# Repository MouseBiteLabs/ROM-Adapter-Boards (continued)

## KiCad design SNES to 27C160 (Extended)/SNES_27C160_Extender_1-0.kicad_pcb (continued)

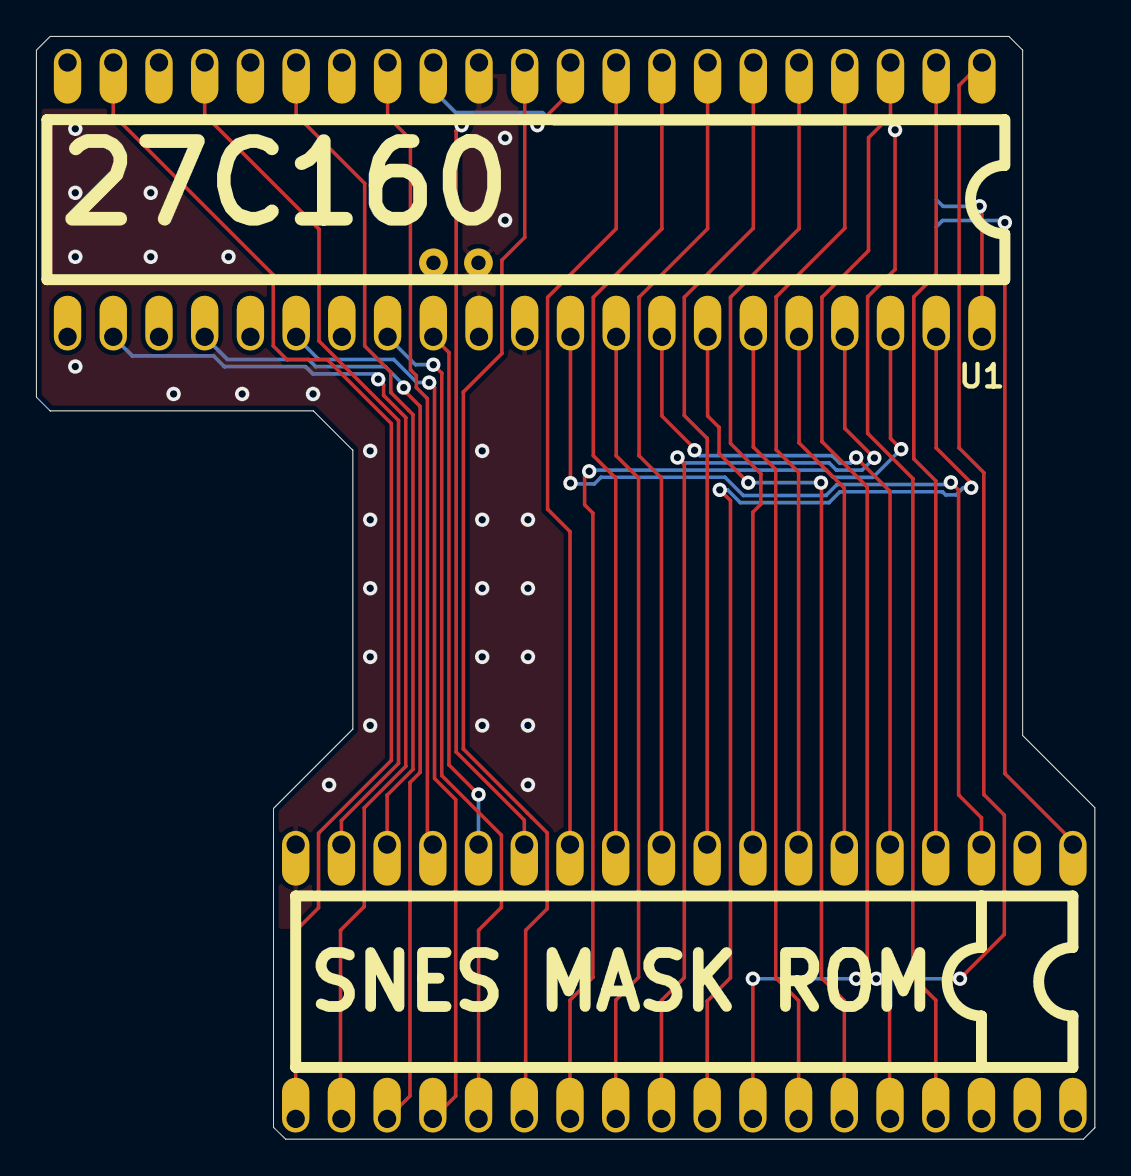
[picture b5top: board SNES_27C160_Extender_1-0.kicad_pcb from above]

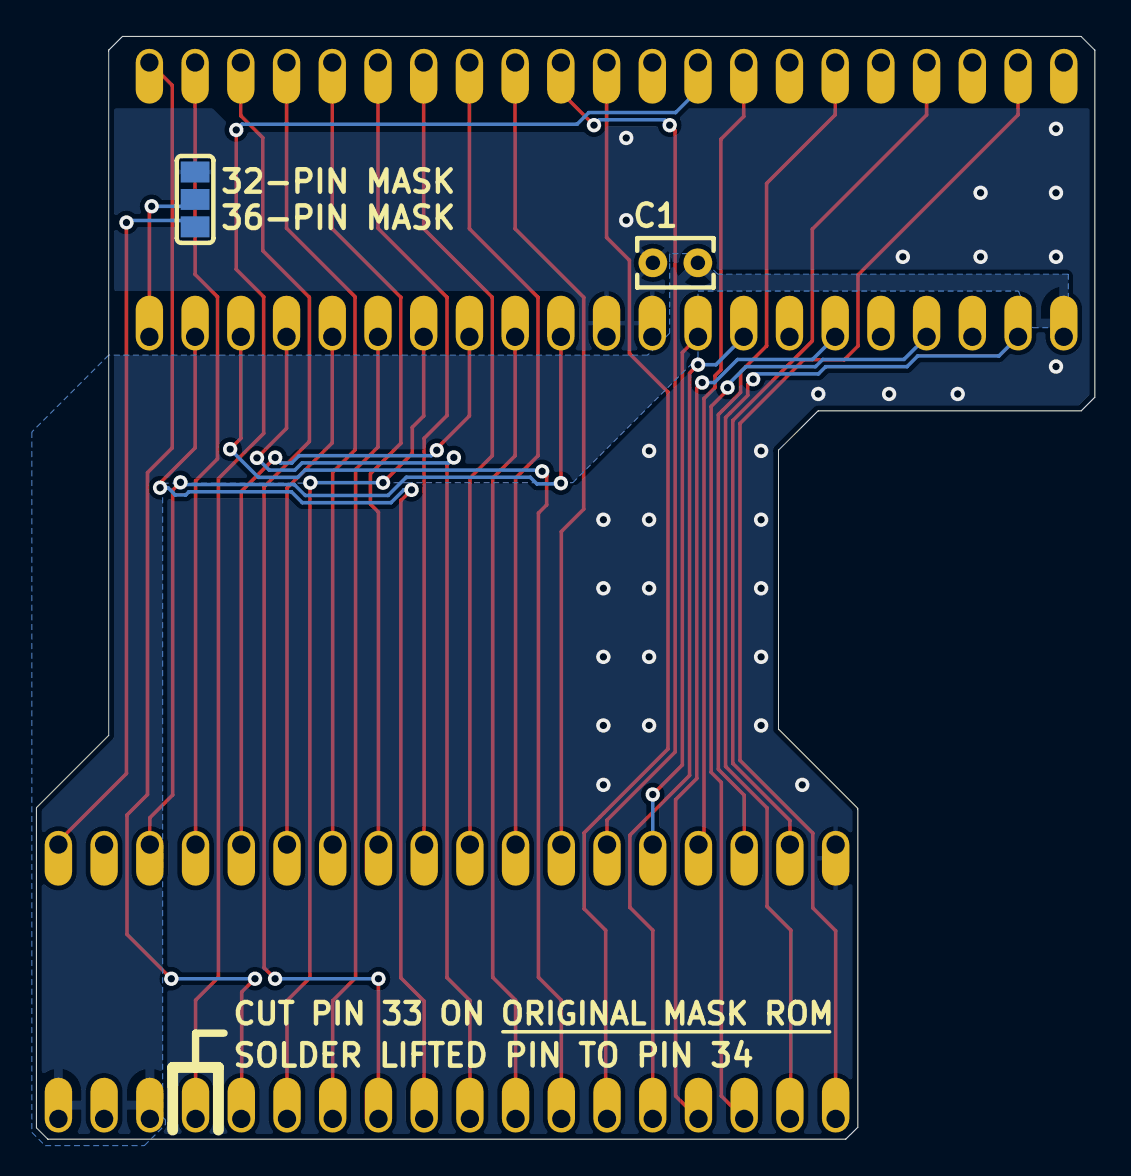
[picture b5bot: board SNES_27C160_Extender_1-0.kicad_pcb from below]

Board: 2 copper layers, 58.8 x 61.3 mm, 4 parts (2 on the bottom side), 34 nets.

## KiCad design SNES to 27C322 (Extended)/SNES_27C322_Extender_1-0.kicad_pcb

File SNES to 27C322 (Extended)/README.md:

# SNES Mask ROM to 27C322 (Extended)

**Design is intended for personal use only, not for modifying existing cartridges for commercial sale.** I really would rather you *not* use these adapter boards to repurpose old carts into rarer games or ROM hacks in order to sell them commercially. Use a brand new cart circuit board instead! I have plenty to choose from :)

Instructions: https://mousebitelabs.com/2020/01/28/27c322-27c160-to-snes-mask-rom-extended-adapter-board/

OSH Park: https://oshpark.com/shared_projects/NkhvILAe (sorry it's expensive but tariffs ain't making these any cheaper from overseas)

## License

<br />This work is licensed under a <a rel="license" href="http://creativecommons.org/licenses/by-sa/4.0/">Creative Commons Attribution-ShareAlike 4.0 International License</a>. You are able to copy and redistribute the material in any medium or format, as well as remix, transform, or build upon the material for any purpose (even commercial) - but you **must** give appropriate credit, provide a link to the license, and indicate if any changes were made.

©MouseBiteLabs 2025

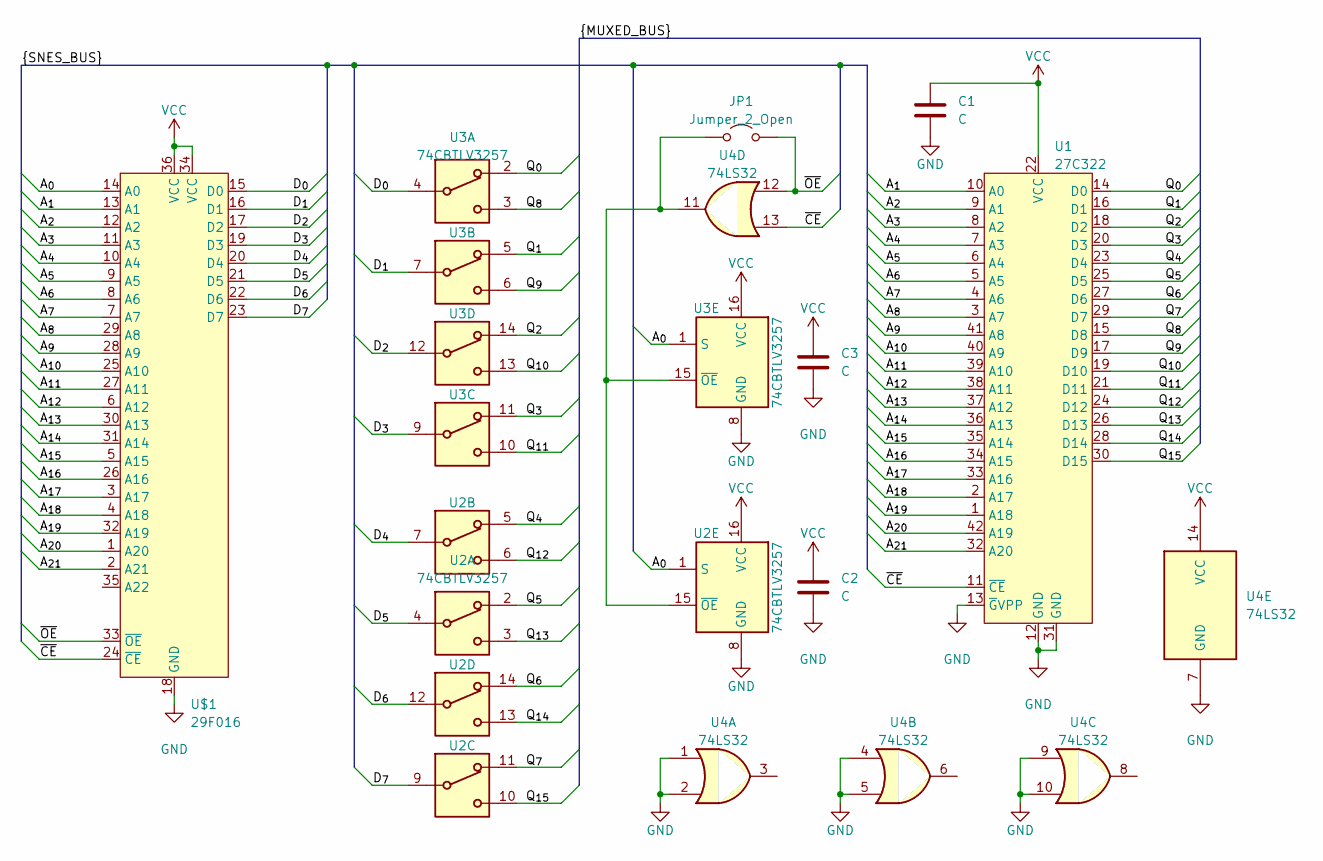
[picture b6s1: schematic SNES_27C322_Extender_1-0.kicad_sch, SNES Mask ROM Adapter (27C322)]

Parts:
C1, C2, C3: C; C_THT
JP1: Jumper_2_Open; SJ
U1: 27C322; PDIP_42_Offset_Pads
U2, U3: 74CBTLV3257; DIP-16_W7.62mm
U4: 74LS32; DIP-14_W7.62mm
U$1: 29F016; 36-PDIP

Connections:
/A_{0}: U2.1 (S), U3.1 (S), U$1.14 (A0)
/A_{1}: U1.10 (A0), U$1.13 (A1)
/A_{2}: U1.9 (A1), U$1.12 (A2)
/A_{3}: U1.8 (A2), U$1.11 (A3)
/A_{4}: U1.7 (A3), U$1.10 (A4)
/A_{5}: U1.6 (A4), U$1.9 (A5)
/A_{6}: U1.5 (A5), U$1.8 (A6)
/A_{7}: U1.4 (A6), U$1.7 (A7)
/A_{8}: U1.3 (A7), U$1.29 (A8)
/A_{9}: U1.41 (A8), U$1.28 (A9)
/A_{10}: U1.40 (A9), U$1.25 (A10)
/A_{11}: U1.39 (A10), U$1.27 (A11)
/A_{12}: U1.38 (A11), U$1.6 (A12)
/A_{13}: U1.37 (A12), U$1.30 (A13)
/A_{14}: U1.36 (A13), U$1.31 (A14)
/A_{15}: U1.35 (A14), U$1.5 (A15)
/A_{16}: U1.34 (A15), U$1.26 (A16)
/A_{17}: U1.33 (A16), U$1.3 (A17)
/A_{18}: U1.2 (A17), U$1.4 (A18)
/A_{19}: U1.1 (A18), U$1.32 (A19)
/A_{20}: U1.42 (A19), U$1.1 (A20)
/A_{21}: U1.32 (A20), U$1.2 (A21)
/D_{0}: U3.4, U$1.15 (D0)
/D_{1}: U3.7, U$1.16 (D1)
/D_{2}: U3.12, U$1.17 (D2)
/D_{3}: U3.9, U$1.19 (D3)
/D_{4}: U2.7, U$1.20 (D4)
/D_{5}: U2.4, U$1.21 (D5)
/D_{6}: U2.12, U$1.22 (D6)
/D_{7}: U2.9, U$1.23 (D7)
/Q_{0}: U1.14 (D0), U3.2
/Q_{1}: U1.16 (D1), U3.5
/Q_{2}: U1.18 (D2), U3.14
/Q_{3}: U1.20 (D3), U3.11
/Q_{4}: U1.23 (D4), U2.5
/Q_{5}: U1.25 (D5), U2.2
/Q_{6}: U1.27 (D6), U2.14
/Q_{7}: U1.29 (D7), U2.11
/Q_{8}: U1.15 (D8), U3.3
/Q_{9}: U1.17 (D9), U3.6
/Q_{10}: U1.19 (D10), U3.13
/Q_{11}: U1.21 (D11), U3.10
/Q_{12}: U1.24 (D12), U2.6
/Q_{13}: U1.26 (D13), U2.3
/Q_{14}: U1.28 (D14), U2.13
/Q_{15}: U1.30 (D15), U2.10
/~CE: U1.11 (~CE), U4.13, U$1.24 (~CE)
/~OE: JP1.2 (B), U4.12, U$1.33 (~OE)
GND: C1.2, C2.2, C3.2, U1.12 (GND), U1.13 (~GVPP), U1.31 (GND), U2.8 (GND), U3.8 (GND), U4.1, U4.2, U4.4, U4.5, U4.7 (GND), U4.9, U4.10, U$1.18 (GND)
unnamed: JP1.1 (A), U2.15 (~OE), U3.15 (~OE), U4.11
VCC: C1.1, C2.1, C3.1, U1.22 (VCC), U2.16 (VCC), U3.16 (VCC), U4.14 (VCC), U$1.34 (VCC), U$1.36 (VCC)

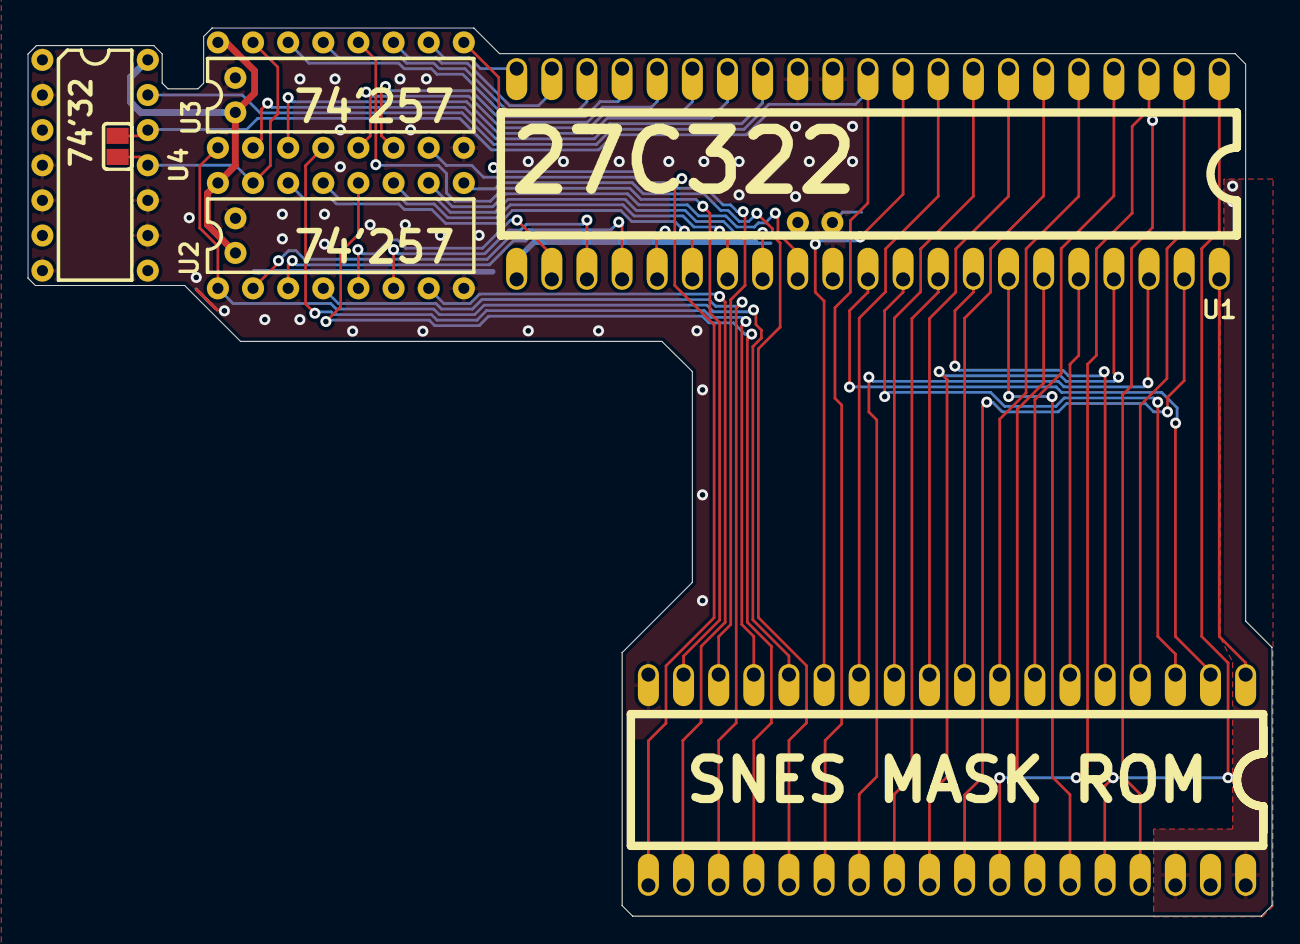
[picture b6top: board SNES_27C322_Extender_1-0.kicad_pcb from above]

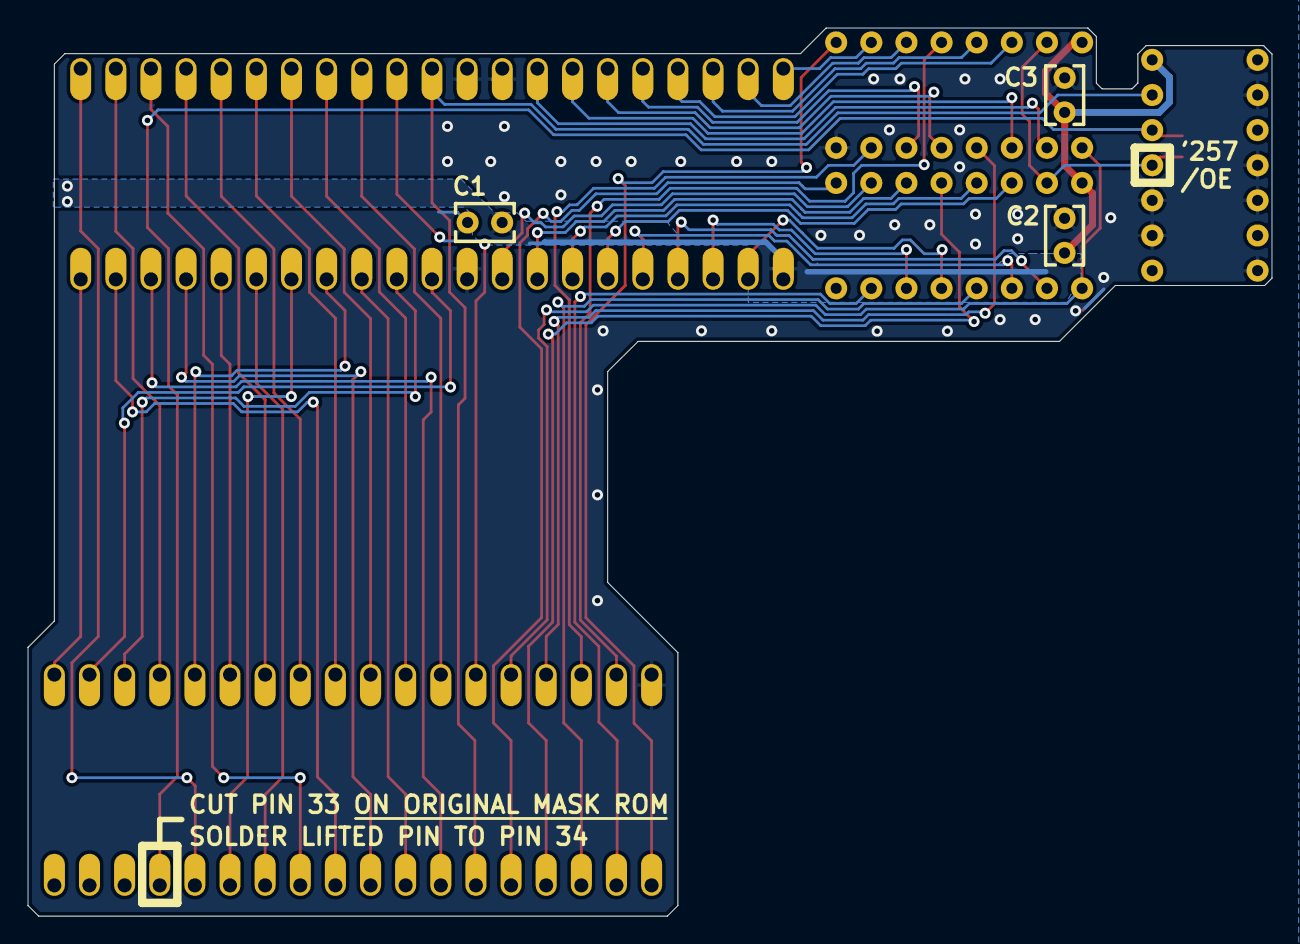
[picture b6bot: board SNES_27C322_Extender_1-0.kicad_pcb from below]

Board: 2 copper layers, 89.9 x 64.2 mm, 9 parts (3 on the bottom side), 51 nets.

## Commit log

2025-05-07 Create SNES to TSOP
